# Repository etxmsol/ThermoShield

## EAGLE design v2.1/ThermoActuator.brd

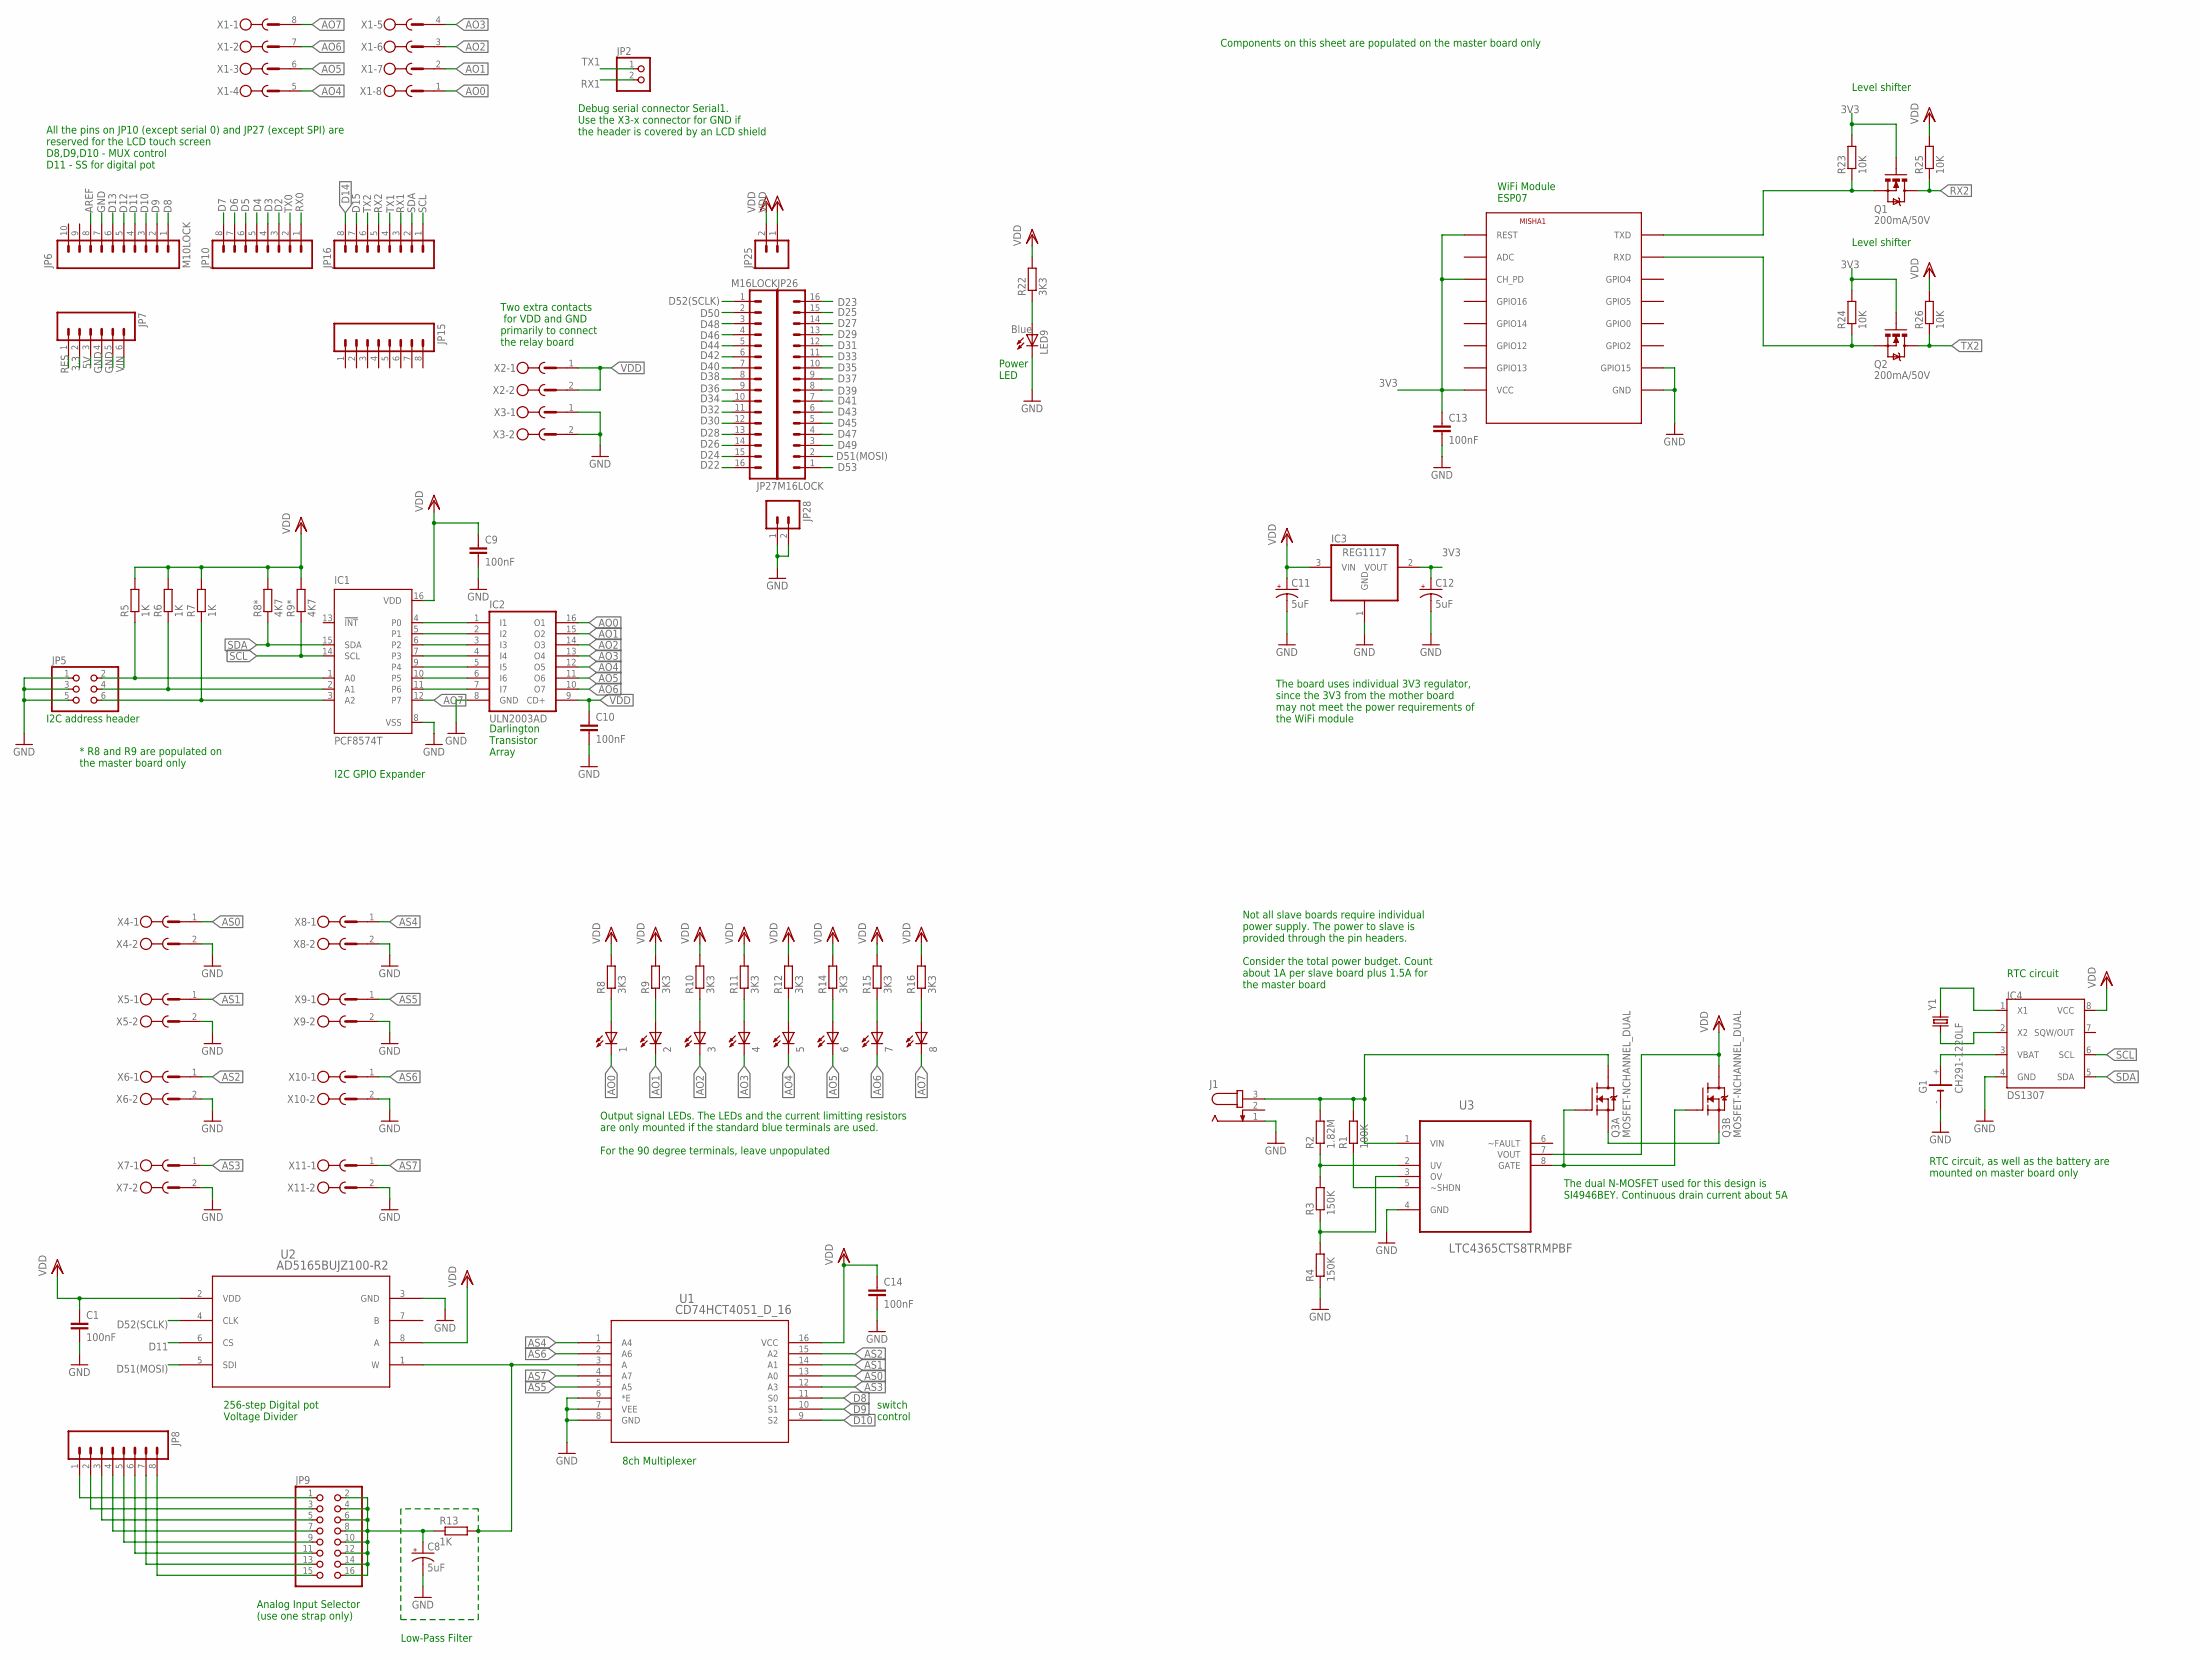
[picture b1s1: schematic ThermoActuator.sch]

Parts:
1, 2, 3, 4, 5, 6, 7, 8: LEDCHIP-LED0805; CHIP-LED0805
C1, C9, C10, C13, C14: 100nF; C0805
C8, C11, C12: 5uF; EIA3216
G1: CH291-1220LF
IC1: PCF8574T; SO16W
IC2: ULN2003AD; SO16
IC3: REG1117; SOT223
IC4: DS1307; SOIC-8
J1: JACK-PLUG1; SPC4078
JP2: PINHD-1X2; 1X02
JP5: PINHD-2X3; 2X03
JP6: M10LOCK; 1X10_LOCK
JP7: M06LOCK; 1X06_LOCK
JP8, JP10, JP15, JP16: M08LOCK; 1X08_LOCK
JP9: PINHD-2X8; 2X08
JP25, JP28: M02LOCK; 1X02_LOCK
JP26, JP27: M16LOCK; 1X16_LOCK
LED9: Blue; CHIP-LED0805
MISHA1: ESP8266-07; ESP-07
Q1, Q2: 200mA/50V; SOT23-3
Q3: MOSFET-NCHANNEL_DUAL; SO08
R1: 100K; R0805
R2: 1.82M; R0805
R3, R4: 150K; R0805
R5, R6, R7: 1K; R0805
R8, R9, R10, R11, R12, R14, R15, R16, R22: 3K3; R0805
R8*, R9*: 4K7; R0805
R13: 1K; R1206
R23, R24, R25, R26: 10K; R0805
U1: CD74HCT4051_D_16; D16
U2: AD5165BUJZ100-R2; UJ_8
U3: LTC4365CTS8TRMPBF; SOT65P280X100-8N
X1: MSTBV8
X2, X3, X4, X5, X6, X7, X8, X9, X10, X11: MSTBV2
Y1: CRYSTAL3.2X1.5MM; CRYSTAL-SMD-3.2X1.5MM

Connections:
3.3: JP7.2
3V3: C12.A (+), C13.1, IC3.2 (VOUT), MISHA1.CH_PD, MISHA1.REST, MISHA1.VCC, Q1.1 (G), Q2.1 (G), R23.2, R24.2
5V: JP7.3
AO0: 1.C, IC2.16 (O1), X1.1
AO1: 2.C, IC2.15 (O2), X1.2
AO2: 3.C, IC2.14 (O3), X1.3
AO3: 4.C, IC2.13 (O4), X1.4
AO4: 5.C, IC2.12 (O5), X1.5
AO5: 6.C, IC2.11 (O6), X1.6
AO6: 7.C, IC2.10 (O7), X1.7
AO7: 8.C, IC1.12 (P7), X1.8
AREF: JP6.8
AS0: U1.13 (A0), X4.1
AS1: U1.14 (A1), X5.1
AS2: U1.15 (A2), X6.1
AS3: U1.12 (A3), X7.1
AS4: U1.1 (A4), X8.1
AS5: U1.5 (A5), X9.1
AS6: U1.2 (A6), X10.1
AS7: U1.4 (A7), X11.1
D2: JP10.3
D3: JP10.4
D4: JP10.5
D5: JP10.6
D6: JP10.7
D7: JP10.8
D8: JP6.1, U1.11 (S0)
D9: JP6.2, U1.10 (S1)
D10: JP6.3, U1.9 (S2)
D11: JP6.4, U2.6 (CS)
D12: JP6.5
D13: JP6.6
D14: JP16.8
D15: JP16.7
D22: JP27.16
D23: JP26.16
D24: JP27.15
D25: JP26.15
D26: JP27.14
D27: JP26.14
D28: JP27.13
D29: JP26.13
D30: JP27.12
D31: JP26.12
D32: JP27.11
D33: JP26.11
D34: JP27.10
D35: JP26.10
D36: JP27.9
D37: JP26.9
D38: JP27.8
D39: JP26.8
D40: JP27.7
D41: JP26.7
D42: JP27.6
D43: JP26.6
D44: JP27.5
D45: JP26.5
D46: JP27.4
D47: JP26.4
D48: JP27.3
D49: JP26.3
D50: JP27.2
D51(MOSI): JP26.2, U2.5 (SDI)
D52(SCLK): JP27.1, U2.4 (CLK)
D53: JP26.1
GND: C1.2, C8.C (-), C9.2, C10.2, C11.C (-), C12.C (-), C13.2, C14.2, G1.-, IC1.8 (VSS), IC2.8 (GND), IC3.1 (GND), IC4.4 (GND), J1.1, JP5.1, JP5.3, JP5.5, JP6.7, JP7.4, JP7.5, JP28.1, JP28.2, LED9.C, MISHA1.GND, MISHA1.GPIO15, R4.1, U1.6 (*E), U1.7 (VEE), U1.8 (GND), U2.3 (GND), U3.4 (GND), X3.1, X3.2, X4.2, X5.2, X6.2, X7.2, X8.2, X9.2, X10.2, X11.2
unnamed: R1.1, U3.5 (~SHDN)
unnamed: R13.2, U1.3 (A), U2.1 (W)
unnamed: IC1.4 (P0), IC2.1 (I1)
unnamed: IC1.5 (P1), IC2.2 (I2)
unnamed: IC1.6 (P2), IC2.3 (I3)
unnamed: IC1.7 (P3), IC2.4 (I4)
unnamed: IC1.9 (P4), IC2.5 (I5)
unnamed: IC1.10 (P5), IC2.6 (I6)
unnamed: IC1.11 (P6), IC2.7 (I7)
unnamed: IC1.1 (A0), JP5.2, R5.1
unnamed: 1.A, R8.1
unnamed: R2.1, R3.2, U3.2 (UV)
unnamed: R3.1, R4.2, U3.3 (OV)
unnamed: Q3.2 (G), Q3.4 (G), U3.8 (GATE)
unnamed: Q3.1 (S), Q3.3 (S)
unnamed: IC4.1 (X1), Y1.P$2 (2)
unnamed: IC4.2 (X2), Y1.P$1 (1)
unnamed: G1.+, IC4.3 (VBAT)
unnamed: 2.A, R9.1
unnamed: IC1.2 (A1), JP5.4, R6.1
unnamed: IC1.3 (A2), JP5.6, R7.1
unnamed: JP8.1, JP9.1
unnamed: JP8.2, JP9.3
unnamed: JP8.3, JP9.5
unnamed: JP8.4, JP9.7
unnamed: JP8.5, JP9.9
unnamed: JP8.6, JP9.11
unnamed: 3.A, R10.1
unnamed: C8.A (+), JP9.2, JP9.4, JP9.6, JP9.8, JP9.10, JP9.12, JP9.14, JP9.16, R13.1
unnamed: JP8.7, JP9.13
unnamed: JP8.8, JP9.15
unnamed: MISHA1.TXD, Q1.2 (S), R23.1
unnamed: MISHA1.RXD, Q2.2 (S), R24.1
unnamed: J1.3, Q3.6 (D1), R1.2, R2.2, U3.1 (VIN)
unnamed: 4.A, R11.1
unnamed: 5.A, R12.1
unnamed: 6.A, R14.1
unnamed: 7.A, R15.1
unnamed: 8.A, R16.1
unnamed: LED9.A, R22.1
RES: JP7.1
RX0: JP10.1
RX1: JP2.2, JP16.3
RX2: JP16.5, Q1.3 (D), R25.1
SCL: IC1.14 (SCL), IC4.6 (SCL), JP16.1, R9*.1
SDA: IC1.15 (SDA), IC4.5 (SDA), JP16.2, R8*.1
TX0: JP10.2
TX1: JP2.1, JP16.4
TX2: JP16.6, Q2.3 (D), R26.1
VDD: C1.1, C9.1, C10.1, C11.A (+), C14.1, IC1.16 (VDD), IC2.9 (CD+), IC3.3 (VIN), IC4.8 (VCC), JP25.1, JP25.2, Q3.8 (D1), R5.2, R6.2, R7.2, R8.2, R8*.2, R9.2, R9*.2, R10.2, R11.2, R12.2, R14.2, R15.2, R16.2, R22.2, R25.2, R26.2, U1.16 (VCC), U2.2 (VDD), U2.8 (A), U3.7 (VOUT), X2.1, X2.2
VIN: JP7.6

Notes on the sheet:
I2C address header
I2C GPIO Expander
Darlington Transistor Array
8ch Multiplexer
Analog Input Selector (use one strap only)
switch control
Level shifter
WiFi Module ESP07
Power LED
The board uses individual 3V3 regulator, since the 3V3 from the mother board may not meet the power requirements of the WiFi module
Components on this sheet are populated on the master board only
* R8 and R9 are populated on the master board only
Not all slave boards require individual power supply. The power to slave is provided through the pin headers. Consider the total power budget. Count about 1A per slave board plus 1.5A for the master board
All the pins on JP10 (except serial 0) and JP27 (except SPI) are reserved for the LCD touch screen D8,D9,D10 - MUX control D11 - SS for digital pot
Low-Pass Filter
Two extra contacts for VDD and GND primarily to connect the relay board
256-step Digital pot Voltage Divider
RTC circuit
The dual N-MOSFET used for this design is SI4946BEY. Continuous drain current about 5A
Debug serial connector Serial1. Use the X3-x connector for GND if the header is covered by an LCD shield
Output signal LEDs. The LEDs and the current limitting resistors are only mounted if the standard blue terminals are used. For the 90 degree terminals, leave unpopulated
RTC circuit, as well as the battery are mounted on master board only

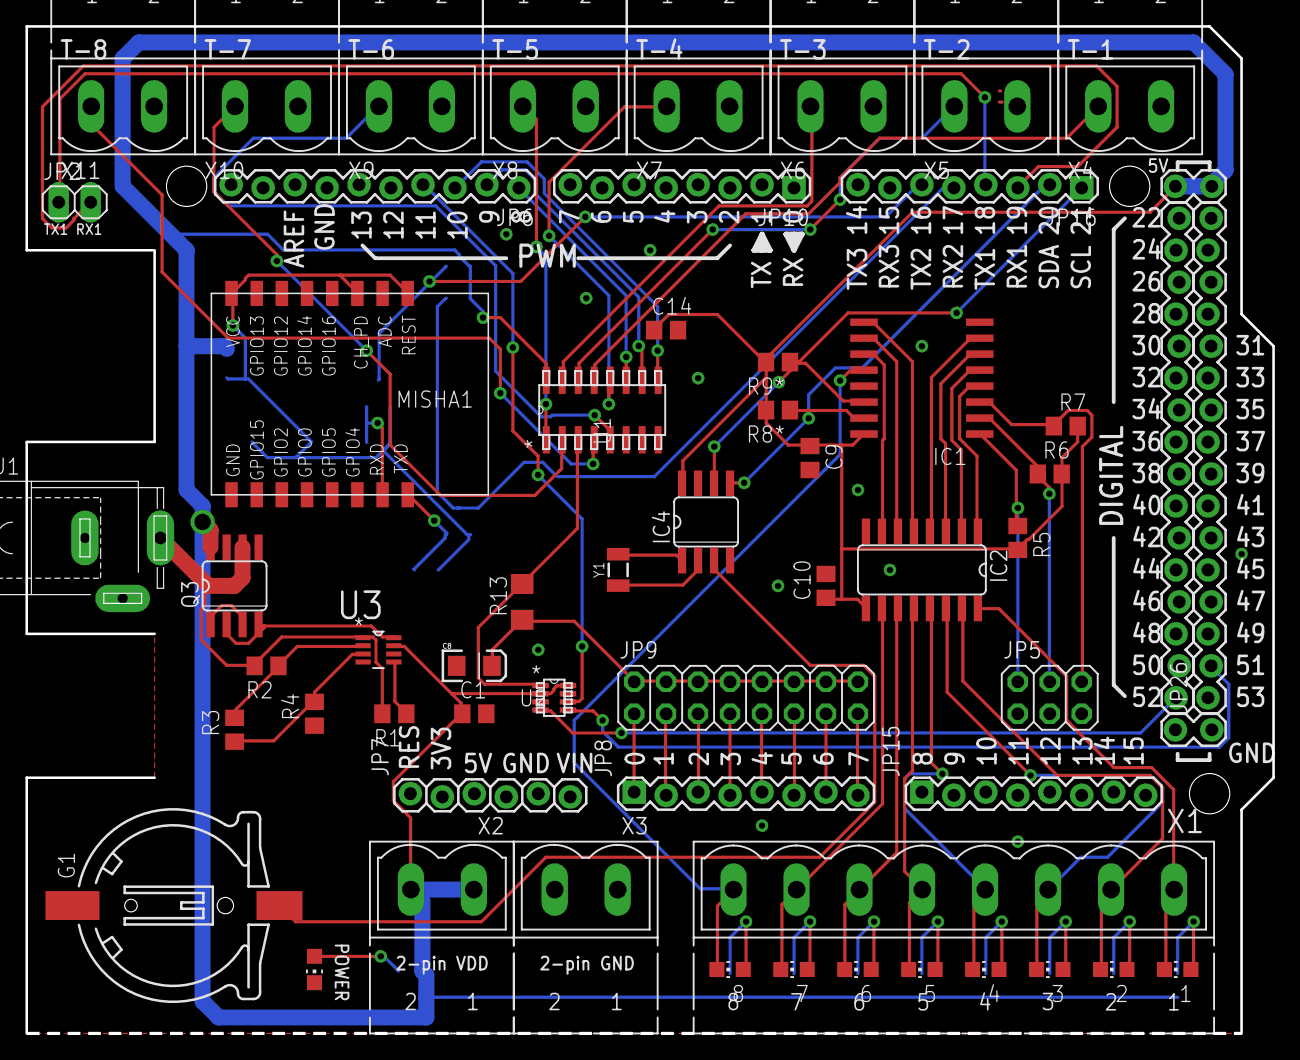
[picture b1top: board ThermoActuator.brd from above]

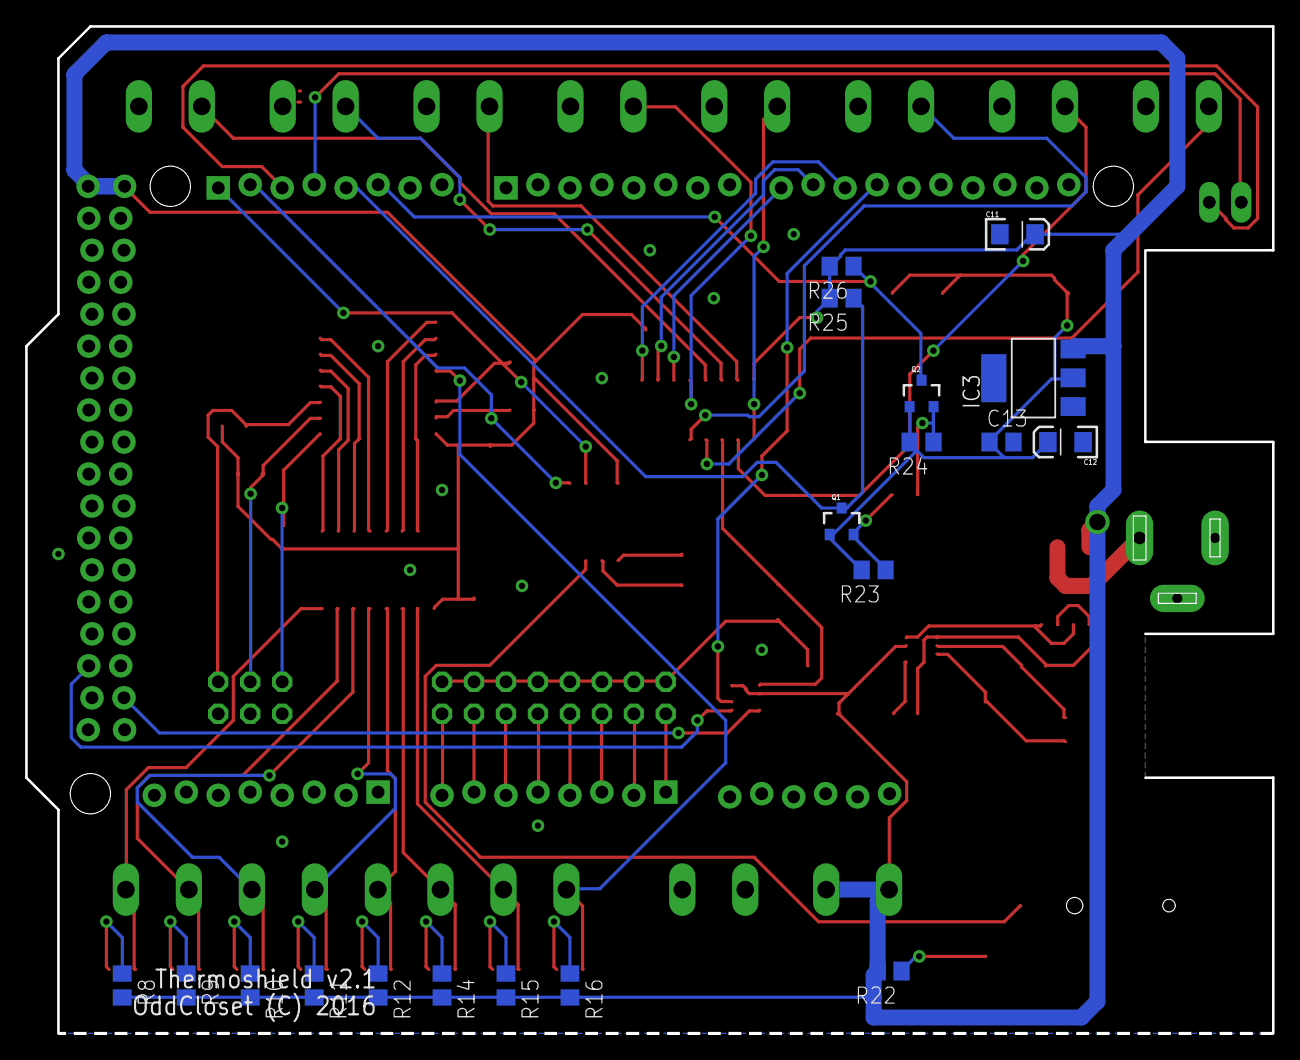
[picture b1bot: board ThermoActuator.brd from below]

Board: 2 copper layers, 99.1 x 80.0 mm, 78 parts (19 on the bottom side), 71 nets.

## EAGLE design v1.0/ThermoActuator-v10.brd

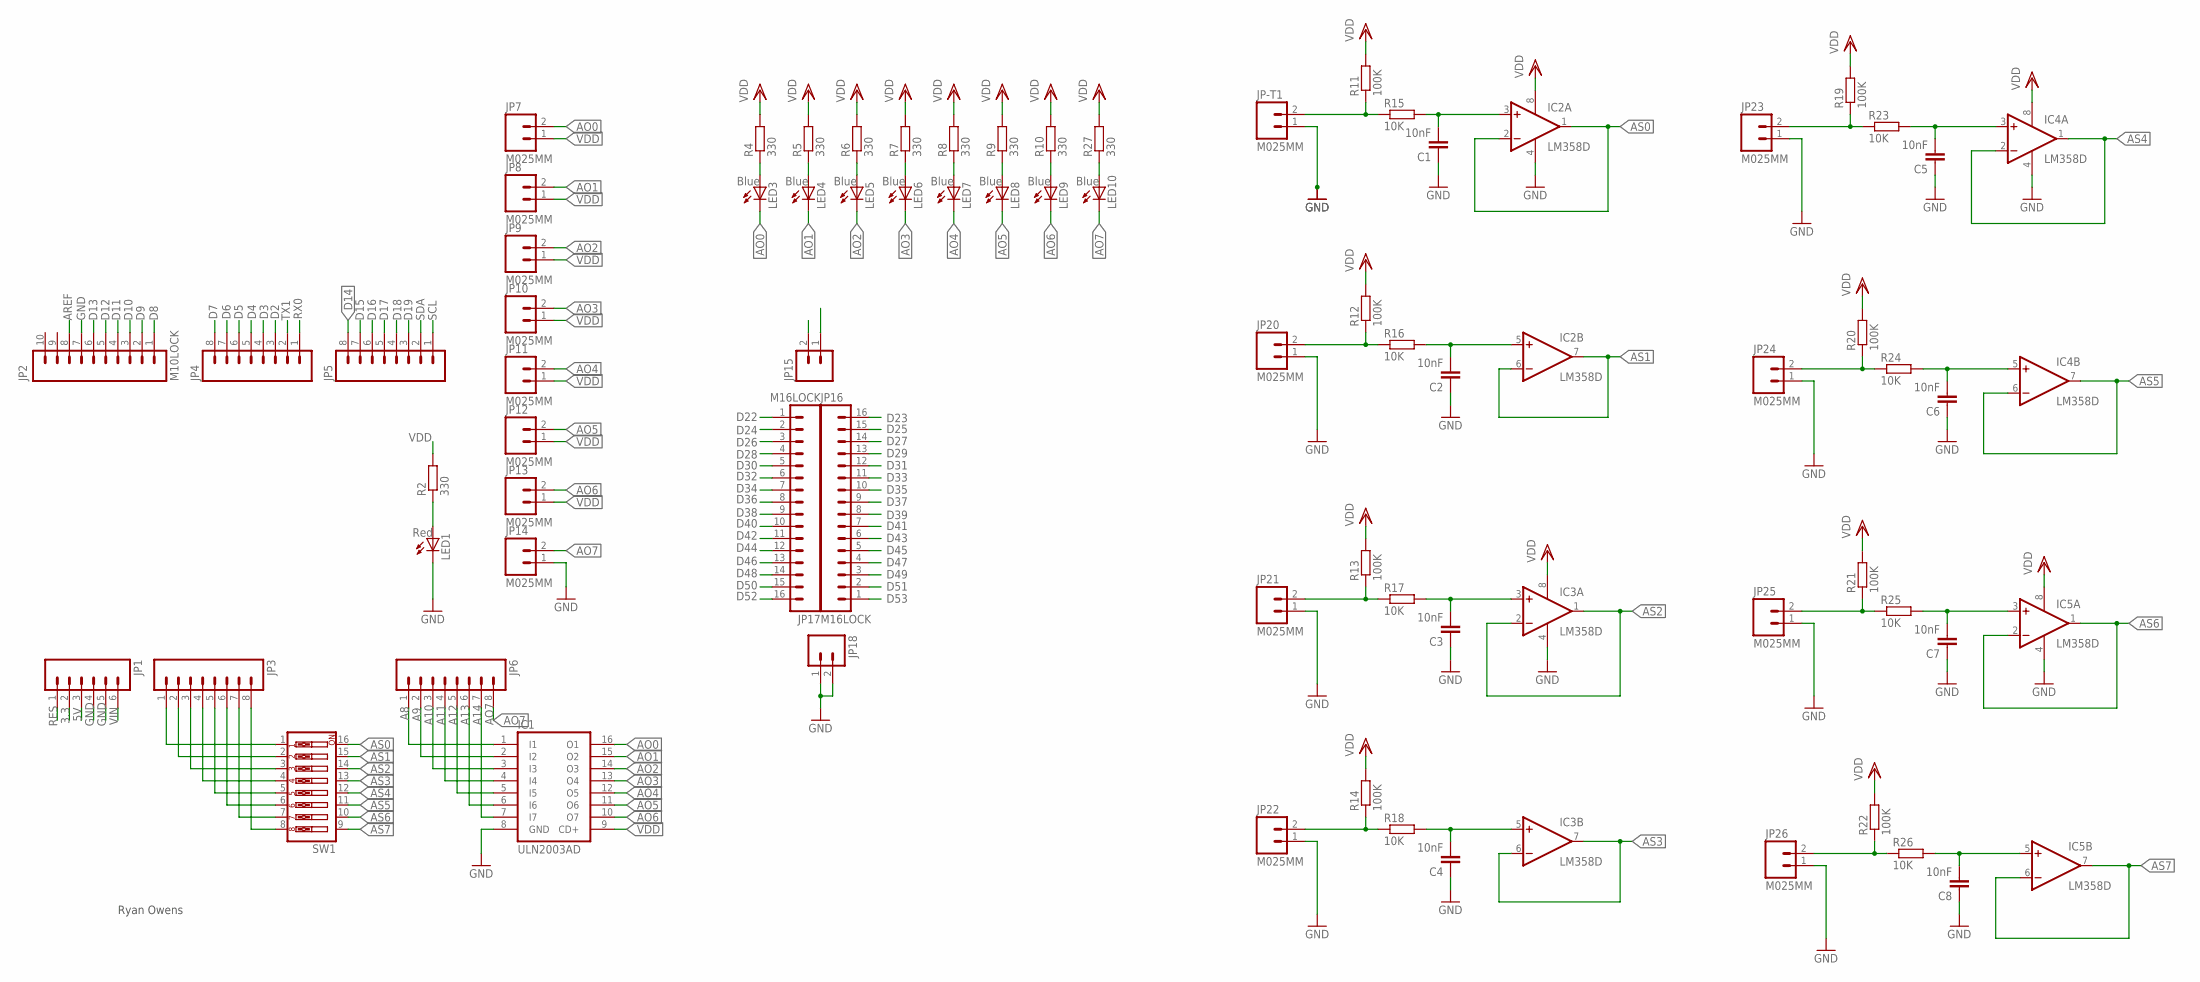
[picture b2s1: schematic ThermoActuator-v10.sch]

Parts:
C1, C2, C3, C4, C5, C6, C7, C8: 10nF; C1206
IC1: ULN2003AD; SO16
IC2, IC3, IC4, IC5: LM358D; SO08
JP1: M06LOCK; 1X06_LOCK
JP2: M10LOCK; 1X10_LOCK
JP3, JP4, JP5, JP6: M08LOCK; 1X08_LOCK
JP7, JP8, JP9, JP10, JP11, JP12, JP13, JP14, JP20, JP21, JP22, JP23, JP24, JP25, JP26: M025MM; SCREWTERMINAL-5MM-2
JP15, JP18: M02LOCK; 1X02_LOCK
JP16, JP17: M16LOCK; 1X16_LOCK
JP-T1: M025MM; SCREWTERMINAL-5MM-2
LED1: Red; CHIP-LED0805
LED3, LED4, LED5, LED6, LED7, LED8, LED9, LED10: Blue; CHIP-LED0805
R2, R4, R5, R6, R7, R8, R9, R10, R27: 330; R0805
R11, R12, R13, R14, R19, R20, R21, R22: 100K; R0805
R15, R16, R17, R18, R23, R24, R25, R26: 10K; R1206
SW1: SW_DIP-8; EDG-08

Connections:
3.3: JP1.2
5V: JP1.3
A8: IC1.1 (I1), JP6.1
A9: IC1.2 (I2), JP6.2
A10: IC1.3 (I3), JP6.3
A11: IC1.4 (I4), JP6.4
A12: IC1.5 (I5), JP6.5
A13: IC1.6 (I6), JP6.6
A14: IC1.7 (I7), JP6.7
AO0: IC1.16 (O1), JP7.2, LED3.C
AO1: IC1.15 (O2), JP8.2, LED4.C
AO2: IC1.14 (O3), JP9.2, LED5.C
AO3: IC1.13 (O4), JP10.2, LED6.C
AO4: IC1.12 (O5), JP11.2, LED7.C
AO5: IC1.11 (O6), JP12.2, LED8.C
AO6: IC1.10 (O7), JP13.2, LED9.C
AO7: JP6.8, JP14.2, LED10.C
AREF: JP2.8
AS0: IC2.1 (OUT), IC2.2 (-IN), SW1.16
AS1: IC2.6 (-IN), IC2.7 (OUT), SW1.15
AS2: IC3.1 (OUT), IC3.2 (-IN), SW1.14
AS3: IC3.6 (-IN), IC3.7 (OUT), SW1.13
AS4: IC4.1 (OUT), IC4.2 (-IN), SW1.12
AS5: IC4.6 (-IN), IC4.7 (OUT), SW1.11
AS6: IC5.1 (OUT), IC5.2 (-IN), SW1.10
AS7: IC5.6 (-IN), IC5.7 (OUT), SW1.9
D2: JP4.3
D3: JP4.4
D4: JP4.5
D5: JP4.6
D6: JP4.7
D7: JP4.8
D8: JP2.1
D9: JP2.2
D10: JP2.3
D11: JP2.4
D12: JP2.5
D13: JP2.6
D14: JP5.8
D15: JP5.7
D16: JP5.6
D17: JP5.5
D18: JP5.4
D19: JP5.3
D22: JP17.1
D23: JP16.16
D24: JP17.2
D25: JP16.15
D26: JP17.3
D27: JP16.14
D28: JP17.4
D29: JP16.13
D30: JP17.5
D31: JP16.12
D32: JP17.6
D33: JP16.11
D34: JP17.7
D35: JP16.10
D36: JP17.8
D37: JP16.9
D38: JP17.9
D39: JP16.8
D40: JP17.10
D41: JP16.7
D42: JP17.11
D43: JP16.6
D44: JP17.12
D45: JP16.5
D46: JP17.13
D47: JP16.4
D48: JP17.14
D49: JP16.3
D50: JP17.15
D51: JP16.2
D52: JP17.16
D53: JP16.1
GND: C1.1, C2.1, C3.1, C4.1, C5.1, C6.1, C7.1, C8.1, IC1.8 (GND), IC2.4 (V-), IC3.4 (V-), IC4.4 (V-), IC5.4 (V-), JP1.4, JP1.5, JP2.7, JP14.1, JP18.1, JP18.2, JP20.1, JP21.1, JP22.1, JP23.1, JP24.1, JP25.1, JP26.1, JP-T1.1, LED1.C
unnamed: JP-T1.2, R11.1, R15.1
unnamed: C1.2, IC2.3 (+IN), R15.2
unnamed: JP3.1, SW1.1
unnamed: JP3.2, SW1.2
unnamed: JP3.3, SW1.3
unnamed: JP3.4, SW1.4
unnamed: JP3.5, SW1.5
unnamed: JP3.6, SW1.6
unnamed: JP3.7, SW1.7
unnamed: JP3.8, SW1.8
unnamed: JP20.2, R12.1, R16.1
unnamed: C2.2, IC2.5 (+IN), R16.2
unnamed: LED3.A, R4.1
unnamed: LED4.A, R5.1
unnamed: LED5.A, R6.1
unnamed: LED6.A, R7.1
unnamed: LED7.A, R8.1
unnamed: LED8.A, R9.1
unnamed: LED9.A, R10.1
unnamed: JP21.2, R13.1, R17.1
unnamed: C3.2, IC3.3 (+IN), R17.2
unnamed: JP22.2, R14.1, R18.1
unnamed: C4.2, IC3.5 (+IN), R18.2
unnamed: JP23.2, R19.1, R23.1
unnamed: C5.2, IC4.3 (+IN), R23.2
unnamed: JP24.2, R20.1, R24.1
unnamed: C6.2, IC4.5 (+IN), R24.2
unnamed: JP25.2, R21.1, R25.1
unnamed: C7.2, IC5.3 (+IN), R25.2
unnamed: JP26.2, R22.1, R26.1
unnamed: C8.2, IC5.5 (+IN), R26.2
unnamed: LED10.A, R27.1
unnamed: LED1.A, R2.1
RES: JP1.1
RX0: JP4.1
SCL: JP5.1
SDA: JP5.2
TX1: JP4.2
VDD: IC1.9 (CD+), IC2.8 (V+), IC3.8 (V+), IC4.8 (V+), IC5.8 (V+), JP7.1, JP8.1, JP9.1, JP10.1, JP11.1, JP12.1, JP13.1, JP15.1, JP15.2, R2.2, R4.2, R5.2, R6.2, R7.2, R8.2, R9.2, R10.2, R11.2, R12.2, R13.2, R14.2, R19.2, R20.2, R21.2, R22.2, R27.2
VIN: JP1.6

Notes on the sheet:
Ryan Owens

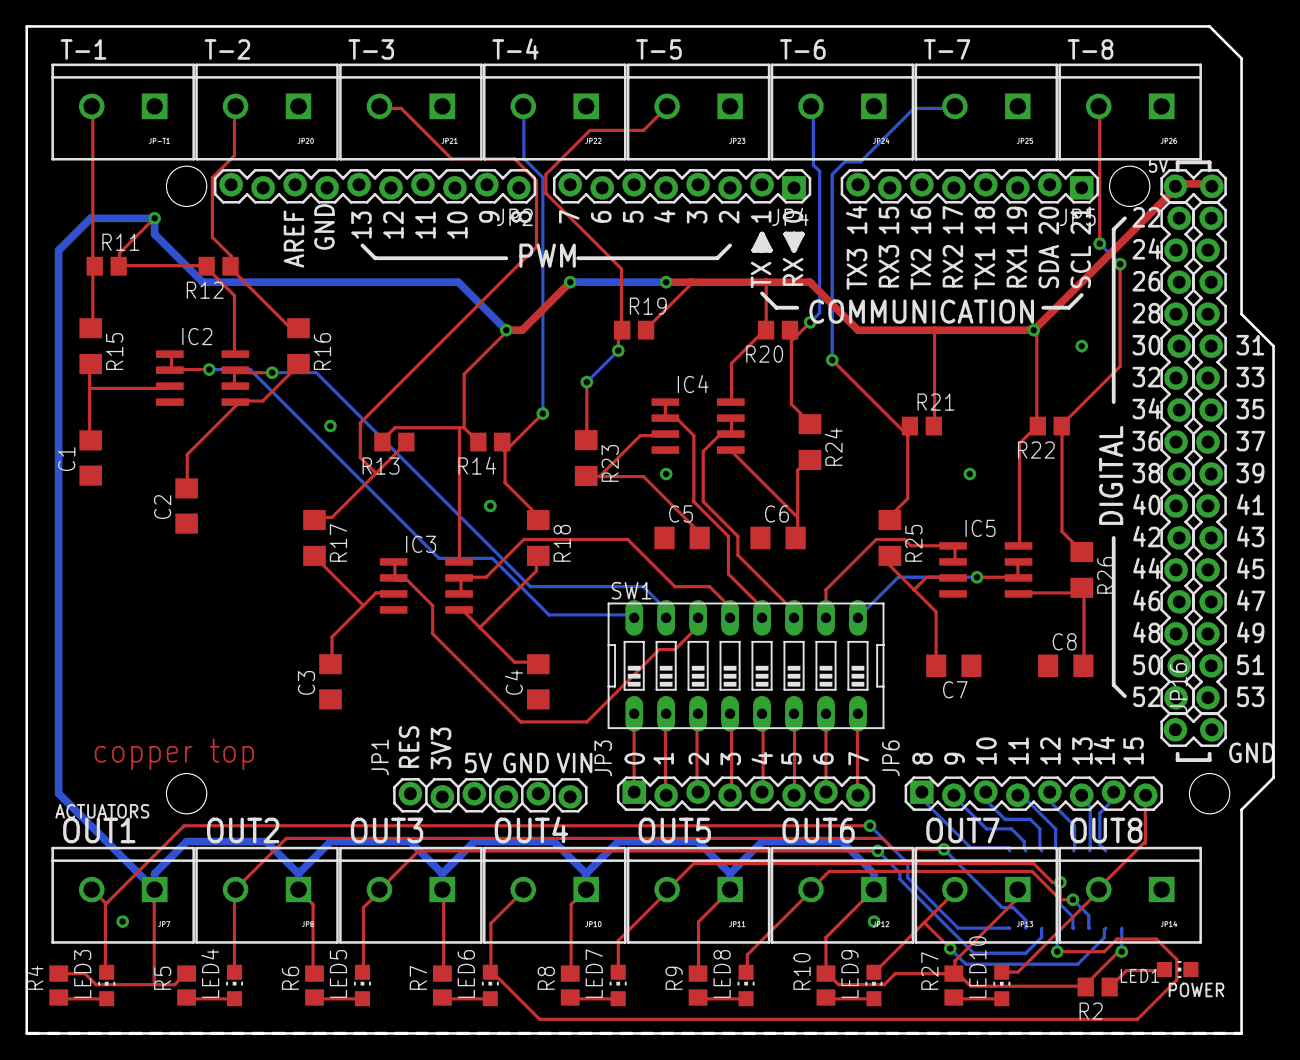
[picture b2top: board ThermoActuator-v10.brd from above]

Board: 2 copper layers, 99.1 x 80.0 mm, 74 parts (1 on the bottom side), 58 nets.

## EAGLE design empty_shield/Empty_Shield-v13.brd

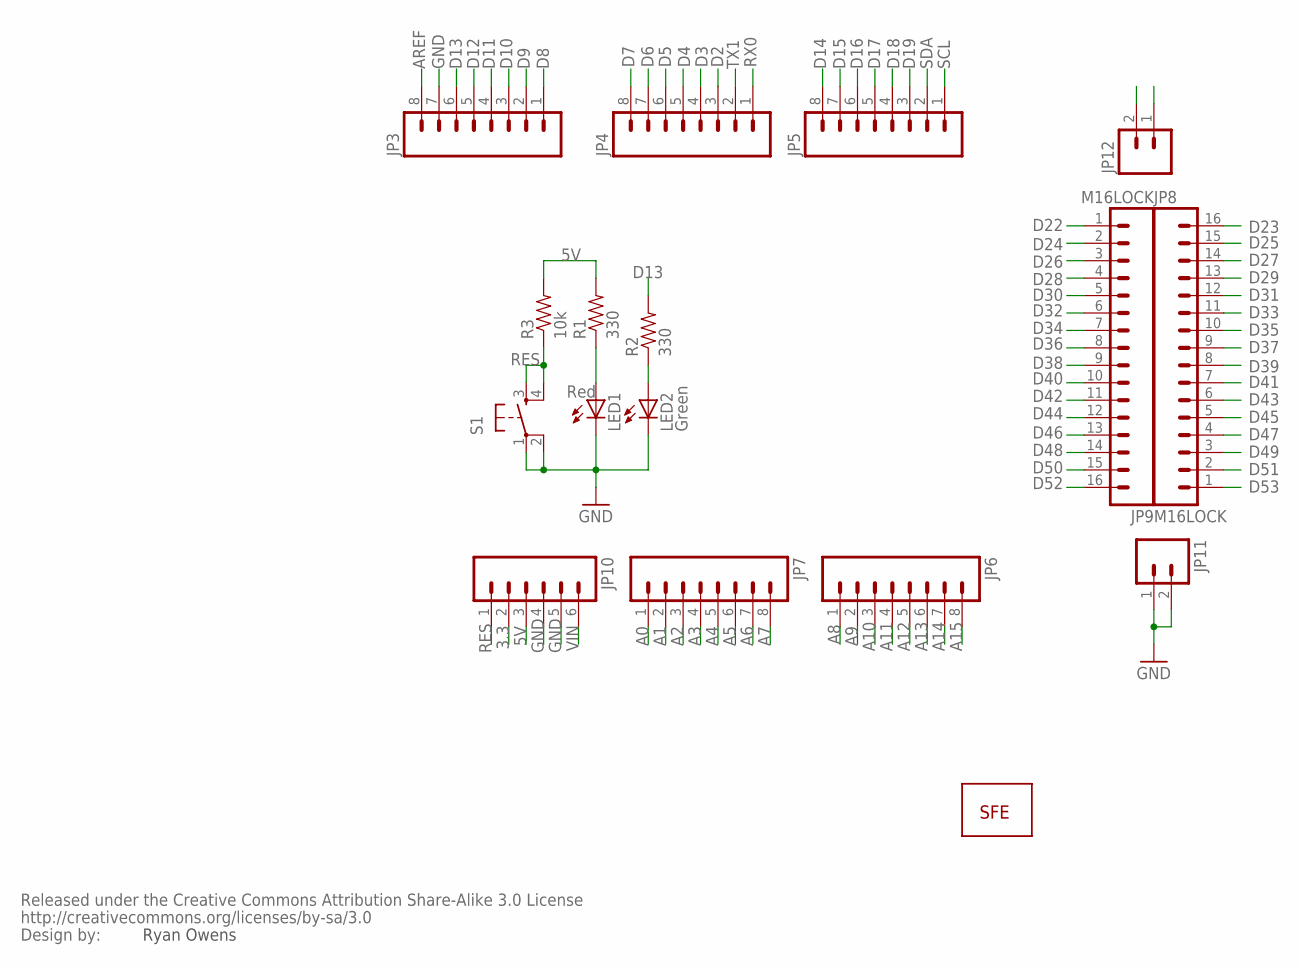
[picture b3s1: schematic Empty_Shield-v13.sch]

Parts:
JP3, JP4, JP5, JP6, JP7: M08LOCK; 1X08_LOCK
JP8, JP9: M16LOCK; 1X16_LOCK
JP10: M06LOCK; 1X06_LOCK
JP11, JP12: M02LOCK; 1X02_LOCK
LED1: Red; LED5MM
LED2: Green; LED5MM
R1, R2: 330; AXIAL-0.3
R3: 10k; AXIAL-0.3
S1: TAC_SWITCHPTH; TACTILE-PTH
U$1: LOGO-SFENEW; SFE-NEW-WEBLOGO
U$2: CREATIVE_COMMONS

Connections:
3.3: JP10.2
5V: JP10.3, R1.P$2 (2), R3.P$2 (2)
5V@1: JP12.1, JP12.2
A0: JP7.1
A1: JP7.2
A2: JP7.3
A3: JP7.4
A4: JP7.5
A5: JP7.6
A6: JP7.7
A7: JP7.8
A8: JP6.1
A9: JP6.2
A10: JP6.3
A11: JP6.4
A12: JP6.5
A13: JP6.6
A14: JP6.7
A15: JP6.8
AREF: JP3.8
D2: JP4.3
D3: JP4.4
D4: JP4.5
D5: JP4.6
D6: JP4.7
D7: JP4.8
D8: JP3.1
D9: JP3.2
D10: JP3.3
D11: JP3.4
D12: JP3.5
D13: JP3.6, R2.P$2 (2)
D14: JP5.8
D15: JP5.7
D16: JP5.6
D17: JP5.5
D18: JP5.4
D19: JP5.3
D22: JP9.1
D23: JP8.16
D24: JP9.2
D25: JP8.15
D26: JP9.3
D27: JP8.14
D28: JP9.4
D29: JP8.13
D30: JP9.5
D31: JP8.12
D32: JP9.6
D33: JP8.11
D34: JP9.7
D35: JP8.10
D36: JP9.8
D37: JP8.9
D38: JP9.9
D39: JP8.8
D40: JP9.10
D41: JP8.7
D42: JP9.11
D43: JP8.6
D44: JP9.12
D45: JP8.5
D46: JP9.13
D47: JP8.4
D48: JP9.14
D49: JP8.3
D50: JP9.15
D51: JP8.2
D52: JP9.16
D53: JP8.1
GND: JP3.7, JP10.4, JP10.5, JP11.1, JP11.2, LED1.K (C), LED2.K (C), S1.1, S1.2
unnamed: LED1.A, R1.P$1 (1)
unnamed: LED2.A, R2.P$1 (1)
RES: JP10.1, R3.P$1 (1), S1.3, S1.4
RX0: JP4.1
SCL: JP5.1
SDA: JP5.2
TX1: JP4.2
VIN: JP10.6

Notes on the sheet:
Ryan Owens

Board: 2 copper layers, 18 parts (0 on the bottom side), 7 nets, no tracks yet.

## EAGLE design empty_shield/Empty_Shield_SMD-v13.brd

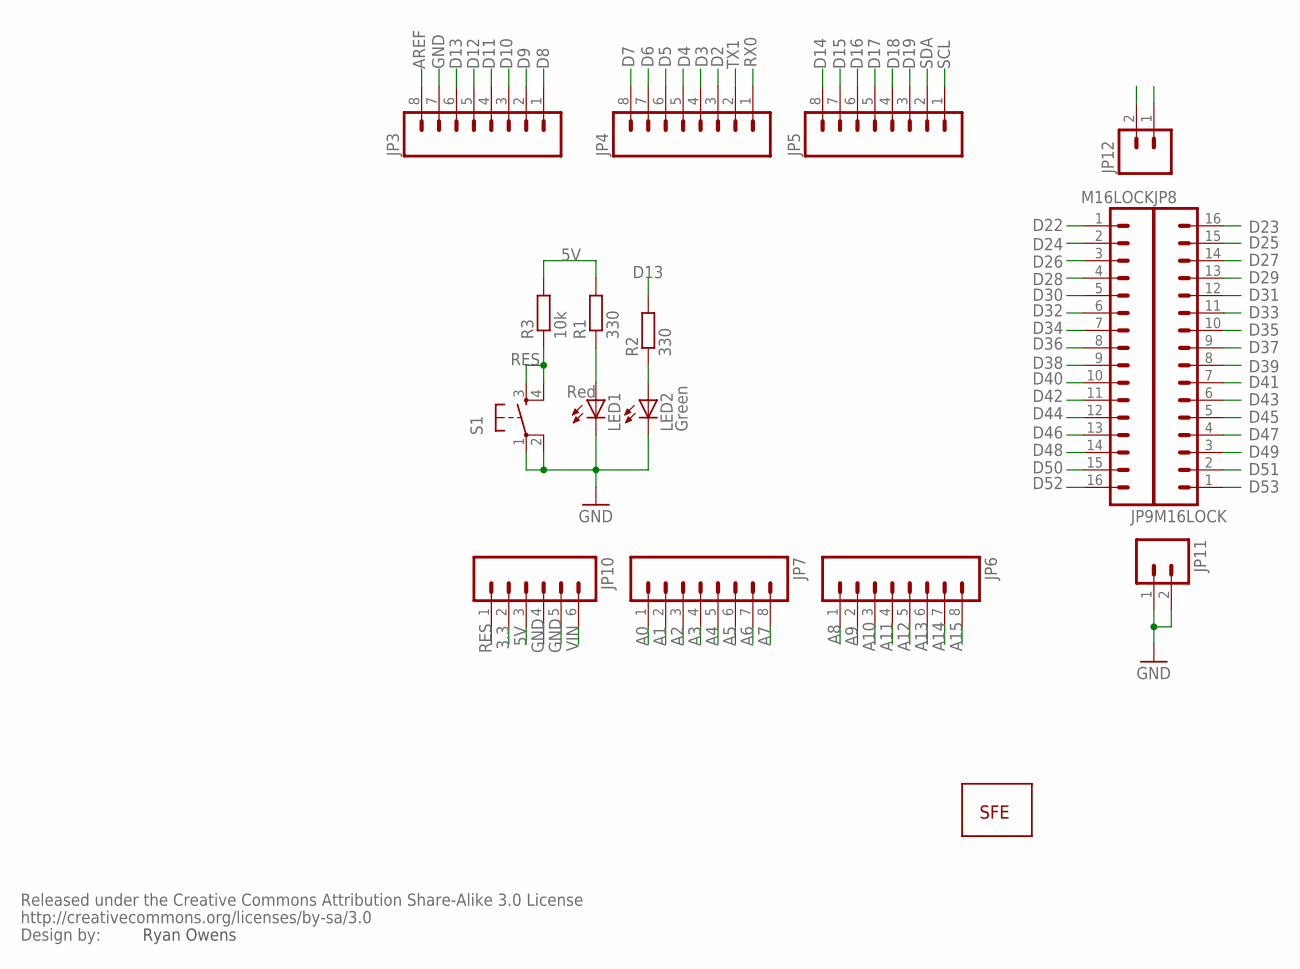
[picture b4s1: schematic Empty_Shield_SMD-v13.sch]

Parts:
JP3, JP4, JP5, JP6, JP7: M08LOCK; 1X08_LOCK
JP8, JP9: M16LOCK; 1X16_LOCK
JP10: M06LOCK; 1X06_LOCK
JP11, JP12: M02LOCK; 1X02_LOCK
LED1: Red; CHIP-LED0805
LED2: Green; CHIP-LED0805
R1, R2: 330; R0805
R3: 10k; R0805
S1: TAC_SWITCHPTH; TACTILE-PTH
U$1: LOGO-SFENEW; SFE-NEW-WEBLOGO
U$2: CREATIVE_COMMONS

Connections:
3.3: JP10.2
5V: JP10.3, R1.2, R3.2
5V@1: JP12.1, JP12.2
A0: JP7.1
A1: JP7.2
A2: JP7.3
A3: JP7.4
A4: JP7.5
A5: JP7.6
A6: JP7.7
A7: JP7.8
A8: JP6.1
A9: JP6.2
A10: JP6.3
A11: JP6.4
A12: JP6.5
A13: JP6.6
A14: JP6.7
A15: JP6.8
AREF: JP3.8
D2: JP4.3
D3: JP4.4
D4: JP4.5
D5: JP4.6
D6: JP4.7
D7: JP4.8
D8: JP3.1
D9: JP3.2
D10: JP3.3
D11: JP3.4
D12: JP3.5
D13: JP3.6, R2.2
D14: JP5.8
D15: JP5.7
D16: JP5.6
D17: JP5.5
D18: JP5.4
D19: JP5.3
D22: JP9.1
D23: JP8.16
D24: JP9.2
D25: JP8.15
D26: JP9.3
D27: JP8.14
D28: JP9.4
D29: JP8.13
D30: JP9.5
D31: JP8.12
D32: JP9.6
D33: JP8.11
D34: JP9.7
D35: JP8.10
D36: JP9.8
D37: JP8.9
D38: JP9.9
D39: JP8.8
D40: JP9.10
D41: JP8.7
D42: JP9.11
D43: JP8.6
D44: JP9.12
D45: JP8.5
D46: JP9.13
D47: JP8.4
D48: JP9.14
D49: JP8.3
D50: JP9.15
D51: JP8.2
D52: JP9.16
D53: JP8.1
GND: JP3.7, JP10.4, JP10.5, JP11.1, JP11.2, LED1.C, LED2.C, S1.1, S1.2
unnamed: LED1.A, R1.1
unnamed: LED2.A, R2.1
RES: JP10.1, R3.1, S1.3, S1.4
RX0: JP4.1
SCL: JP5.1
SDA: JP5.2
TX1: JP4.2
VIN: JP10.6

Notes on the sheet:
Ryan Owens

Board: 2 copper layers, 18 parts (0 on the bottom side), 7 nets, no tracks yet.

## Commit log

2015-09-25 the base for the project
2015-09-25 template shield
2015-09-25 empty shield SMD
2015-09-25 Empty MEGA SMD shield template
2015-09-25 ThermoActuator shield created from the template
2015-09-26 one thermistor ch laid out
2015-09-26 two channels laid out
2015-09-27 shield centered
2015-09-27 centered with the right edge untouched
2015-09-27 lower edge extended
2015-10-05 4 ADC channels and 8 actuators
    somewhat messy, 20 vias. The sparkfun's recommended drc used
2015-10-05 down to 126 DRC errors
2015-10-06 all channels laid out
    somewhat inconsistent but all elements
    laid out except the button
2015-10-07 local autorouting, no ripup *
    almost done. Removed the reset button. Will not be used
    on this shield (a higher shield will have it). Laying out
    VDD route. Only local auto-route from now on
2015-10-08 relay power manual route
    this commit fixes one flipped connector, lines up
    the connectors on 0,1mm grid (as per Mega board)
    the board is almost ready for ordering
2015-10-10 button removed. Ready for manufacturing
    the button is removed. It will sit on the top layer (RTC & SD shield)
    Screw terminals replace with pitch 5.
    Thermistor terminals moved to upper lane
    the board is ready for production, a request for quotation is sent
2015-10-10 SW project created
2015-10-21 SW implementation: class Button
2015-10-21 spice simulation for Thermistor
2015-10-21 AdcChannel class (not fully)
2015-11-02 fixed label alignment on OUTx
2015-11-05 all major func implemented
    cleanup remains
2015-11-09 Everything works and is documented
2015-11-09 cleanup of dated items
2015-11-09 Documents stored
    the documents stored before paper copy go recycle. One bug is fixed. When
    no active channels are configured the program hangs at advance
2015-11-11 The button class documented
2015-11-12 Introduced special handling for OUT7
    The 8th output for actuator is connected directly to the
    relay board, because ULN2003 has 7 channels only. This
    requires the invertion for this actuator channel
2015-11-16 bug fix for empty config.txt
    when an SD card inserted had no config.txt, an empty file
    is created, instead of the default config
2015-11-16 Adding header to the config.txt
    if the config.txt is not found, a new file created with a header
    with some guidelines
2015-11-16 Alarm on storage.begin failure
    adding one alarm (LED) even on storage initialization failure.
    This can only occur on parsing error. More info should be
    obtained over the Serial1 (pin 18, 19)
2015-11-19 Nasty routing error fixed
    The CH5 and CH6 did not work. That was because of one
    unobserved airwire. The ground was not routed to the IC4. Too bad
    On the boards the airwire must be mounted connecting the ground on C5
    with the pin 4 of the IC4
    The .brd is updated with one extra via, but because the boards are
    already manufactured, there is nothing that can be redone. Solder a
2015-11-19 Saving forced states
    this is primarily to sort out storing the forced states of the
    ADCs (FORCE ON, FORCE OFF and NORMAL). I've decided to only store them in
    EEPROM. Whenever the EEPROM config is valid, the force state is used
    even if the SD config has changed.
    The config.txt has got a header with neccesary explanations. The parser somewhat
    improved (but still simple)
2015-11-30 A final cleanup
2015-11-30 added activity ratio to the logging string
2016-01-17 calibration is added
    this version is for the 10K NTC thermistor. The board is
    populated with low-pass (tantalum) RC filter
2016-02-11 Start schematics of the v2.0
2016-02-16 PCF8574 schematics ready
    schematics for the I2C GPIO expander is completed
2016-02-18 8ch mux routing complete
2016-02-21 PCB caped for lower profile
    two capes are cut. All components are thrown on the PCB
2016-02-25 to the fab
2016-05-03 ThermoShield v2.1
    a new version with WiFi support and cloud capabilities
2016-05-04 routing complete, LEDs are back
2016-06-04 digital pot ad5165
    better choice is a 4 or 6 channel POT. AD5204, AD5206.
    Available on eBay and can be serialized for higher values.
    Well, too late
2016-06-04 Digital Pot AD5165
    apart from the simple support for the digital POT, it was
    discovered that the double row header 38-pin was not correctly
    pin-mapped on the shield. This caused the SPI CLK would be
    connected to D22, instead of D52. Now, this is corrected, but...
    too late:)
2016-06-13 switching digital POT
    not yet successful
2016-06-16 web configure R0 and Beta
    the item.php is extended to contain the parameters of
    the connected NTCs. The calibration value is also added to
    the web interface

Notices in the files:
v2.1/ThermoActuator.brd:
OddCloset (C) 2016
parts and their libraries:
SparkFun: Released under the Creative Commons Attribution Share-Alike 3.0 License
SparkFun: http://creativecommons.org/licenses/by-sa/3.0
SparkFun-Connectors: Licensing: Creative Commons ShareAlike 4.0 International - https://creativecommons.org/licenses/by-sa/4.0
